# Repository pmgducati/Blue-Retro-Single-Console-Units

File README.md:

# Blue-Retro-Single-Console-Units

This is a collection of PCBs that I made to work with darthcloud's BlueRetro Project. (https://github.com/darthcloud/BlueRetro) The PCB's were created in Eagle and I have included the Gerbers if you would like to create them yourself.

Currently I have NES, Nintendo 64, Gamecube, Sega Saturn, 3DO, PSX/PS2 and PCEngine/Turbografx 16 complete.

I have created PCB's for other supported systems (Listed Below) but have not tested them as I do not have the sytems. I have created a issue for each of the systems that I do not have to test. If you make one please comment in the related issue on any progress/problems.

I am working through Virtual Boy but need to find a cost efficient way to connect it to the Virtual Boy as I am not consolizing mine.

Here is the current status of all systems:

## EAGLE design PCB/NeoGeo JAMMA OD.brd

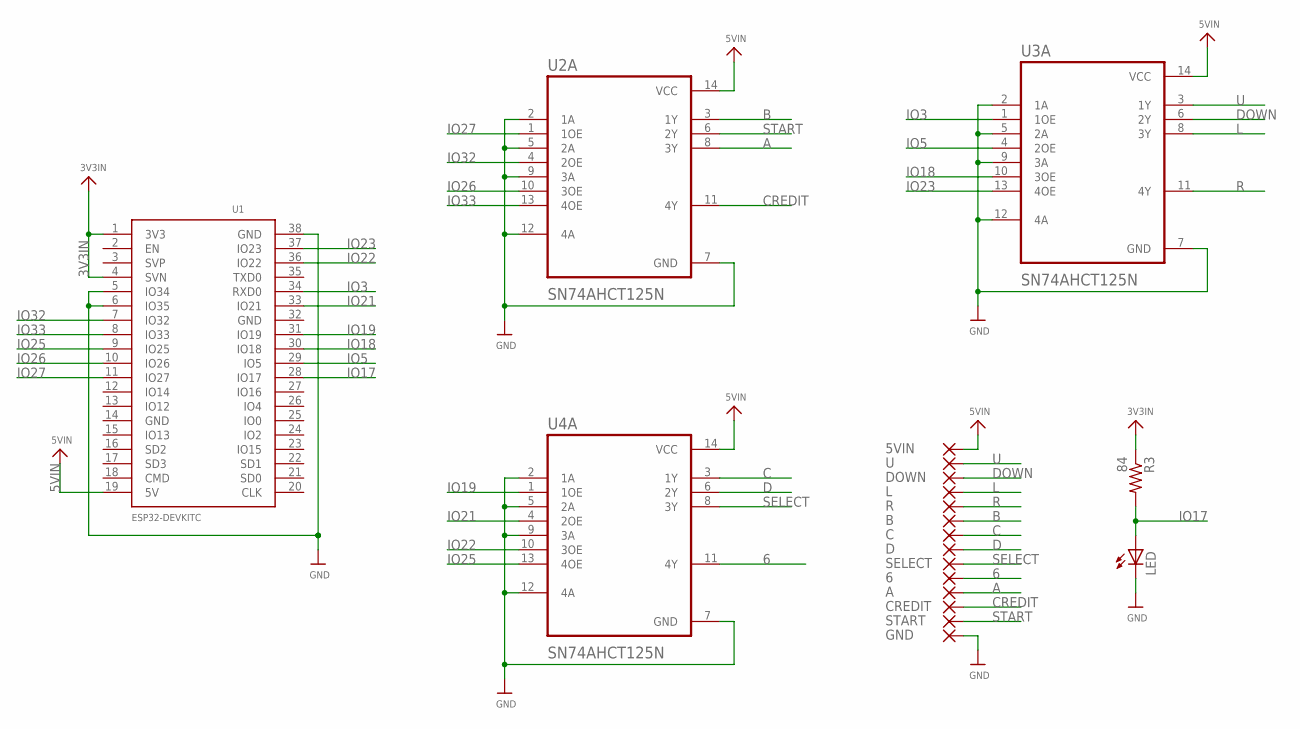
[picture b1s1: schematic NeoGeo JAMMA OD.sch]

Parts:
5VIN, 6: SMD5; SMD2,54-5,08
A: SMD5; SMD2,54-5,08
B: SMD5; SMD2,54-5,08
C: SMD5; SMD2,54-5,08
CREDIT: SMD5; SMD2,54-5,08
D: SMD5; SMD2,54-5,08
DOWN: SMD5; SMD2,54-5,08
GND: SMD5; SMD2,54-5,08
L: SMD5; SMD2,54-5,08
LED: LEDCHIPLED_1206; CHIPLED_1206
R: SMD5; SMD2,54-5,08
R3: 84; R1206
SELECT: SMD5; SMD2,54-5,08
START: SMD5; SMD2,54-5,08
U: SMD5; SMD2,54-5,08
U1: ESP32DEVKITC; ESP32-DEVKITC
U2A, U3A, U4A: SN74AHCT125N; DIP794W45P254L1969H508Q14

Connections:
3V3IN: R3.1, U1.1 (3V3), U1.4 (SVN)
5VIN: 5VIN.1, U1.19 (5V), U2A.14 (VCC), U3A.14 (VCC), U4A.14 (VCC)
6: 6.1, U4A.11 (4Y)
A: A.1, U2A.8 (3Y)
B: B.1, U2A.3 (1Y)
C: C.1, U4A.3 (1Y)
CREDIT: CREDIT.1, U2A.11 (4Y)
D: D.1, U4A.6 (2Y)
DOWN: DOWN.1, U3A.6 (2Y)
GND: GND.1, LED.C, U1.5 (IO34), U1.6 (IO35), U1.38 (GND), U2A.2 (1A), U2A.5 (2A), U2A.7 (GND), U2A.9 (3A), U2A.12 (4A), U3A.2 (1A), U3A.5 (2A), U3A.7 (GND), U3A.9 (3A), U3A.12 (4A), U4A.2 (1A), U4A.5 (2A), U4A.7 (GND), U4A.9 (3A), U4A.12 (4A)
IO3: U1.34 (RXD0), U3A.1 (1OE)
IO5: U1.29 (IO5), U3A.4 (2OE)
IO17: LED.A, R3.2, U1.28 (IO17)
IO18: U1.30 (IO18), U3A.10 (3OE)
IO19: U1.31 (IO19), U4A.1 (1OE)
IO21: U1.33 (IO21), U4A.4 (2OE)
IO22: U1.36 (IO22), U4A.10 (3OE)
IO23: U1.37 (IO23), U3A.13 (4OE)
IO25: U1.9 (IO25), U4A.13 (4OE)
IO26: U1.10 (IO26), U2A.10 (3OE)
IO27: U1.11 (IO27), U2A.1 (1OE)
IO32: U1.7 (IO32), U2A.4 (2OE)
IO33: U1.8 (IO33), U2A.13 (4OE)
L: L.1, U3A.8 (3Y)
R: R.1, U3A.11 (4Y)
SELECT: SELECT.1, U4A.8 (3Y)
START: START.1, U2A.6 (2Y)
U: U.1, U3A.3 (1Y)

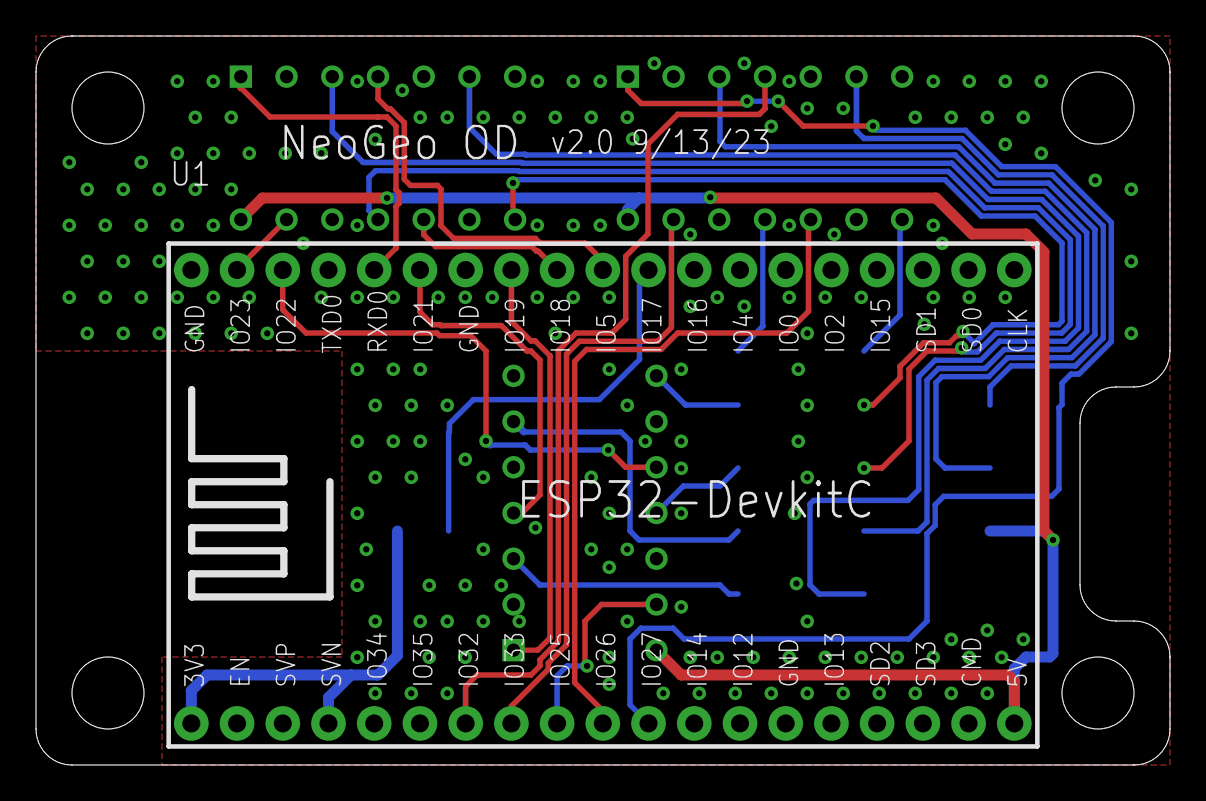
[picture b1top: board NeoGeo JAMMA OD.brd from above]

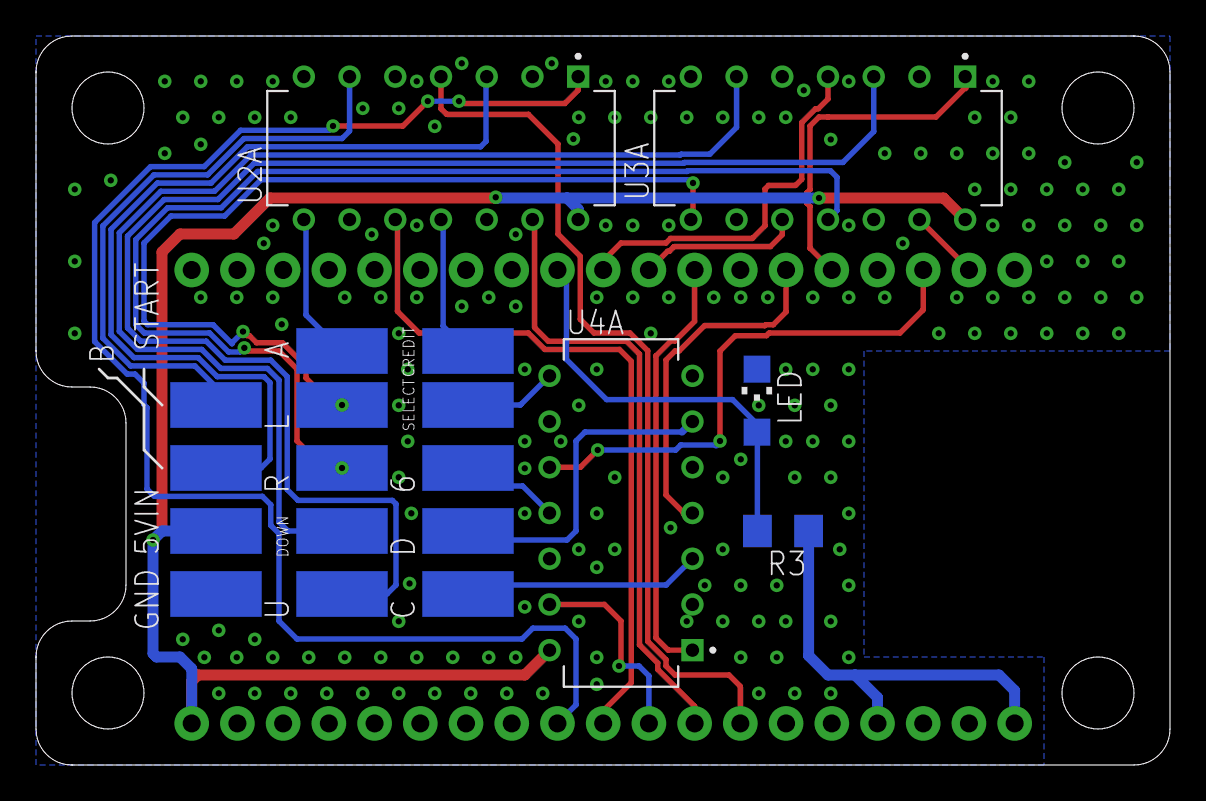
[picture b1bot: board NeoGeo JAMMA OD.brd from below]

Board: 2 copper layers, 63.0 x 40.5 mm, 20 parts (19 on the bottom side), 28 nets.

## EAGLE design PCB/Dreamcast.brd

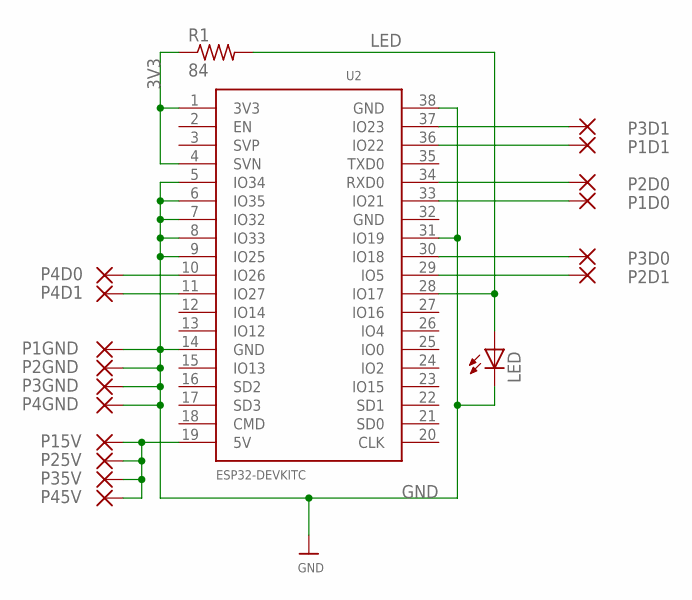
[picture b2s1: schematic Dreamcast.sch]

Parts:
LED: LEDCHIPLED_1206; CHIPLED_1206
P1D0, P1D1, P1GND, P2D0, P2D1, P2GND, P3D0, P3D1, P3GND, P4D0, P4D1, P4GND, P15V, P25V, P35V, P45V: SMD5; SMD2,54-5,08
R1: 84; R1206
U2: ESP32DEVKITC; ESP32-DEVKITC

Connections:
3V3: R1.1, U2.1 (3V3), U2.4 (SVN)
5V: P15V.1, P25V.1, P35V.1, P45V.1, U2.19 (5V)
GND: LED.C, P1GND.1, P2GND.1, P3GND.1, P4GND.1, U2.5 (IO34), U2.6 (IO35), U2.7 (IO32), U2.8 (IO33), U2.9 (IO25), U2.14 (GND), U2.31 (IO19), U2.38 (GND)
LED: LED.A, R1.2, U2.28 (IO17)
P1D0: P1D0.1, U2.33 (IO21)
P1D1: P1D1.1, U2.36 (IO22)
P2D0: P2D0.1, U2.34 (RXD0)
P2D1: P2D1.1, U2.29 (IO5)
P3D0: P3D0.1, U2.30 (IO18)
P3D1: P3D1.1, U2.37 (IO23)
P4D0: P4D0.1, U2.10 (IO26)
P4D1: P4D1.1, U2.11 (IO27)

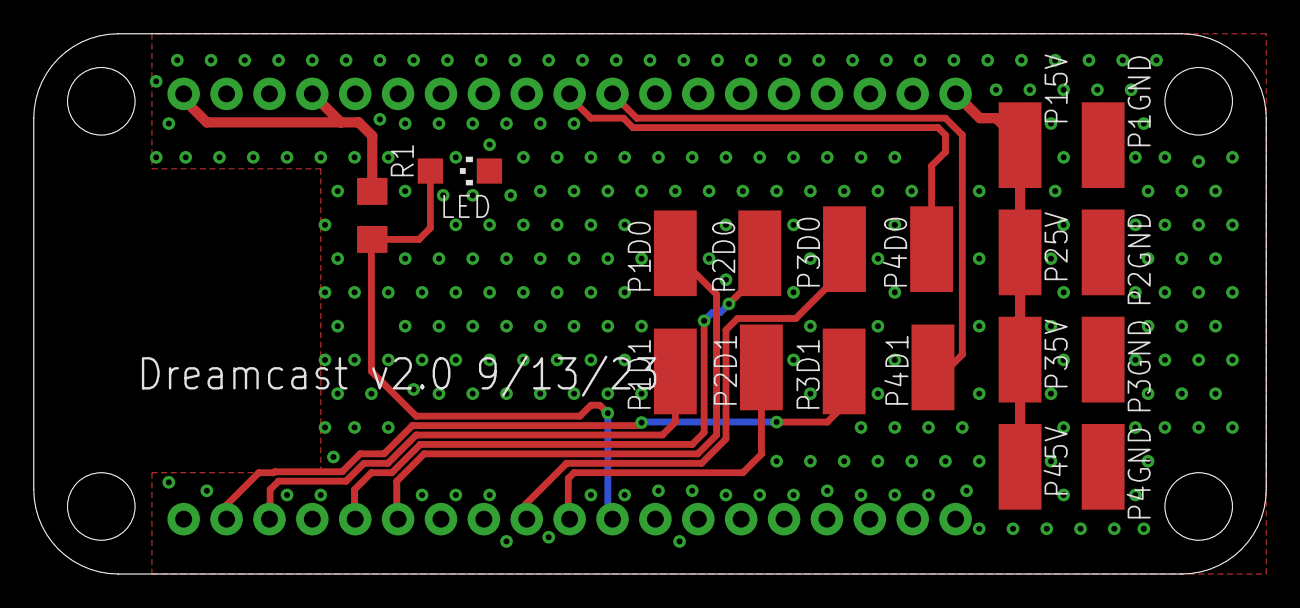
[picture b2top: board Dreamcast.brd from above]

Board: 2 copper layers, 73.0 x 32.0 mm, 19 parts (1 on the bottom side), 12 nets.

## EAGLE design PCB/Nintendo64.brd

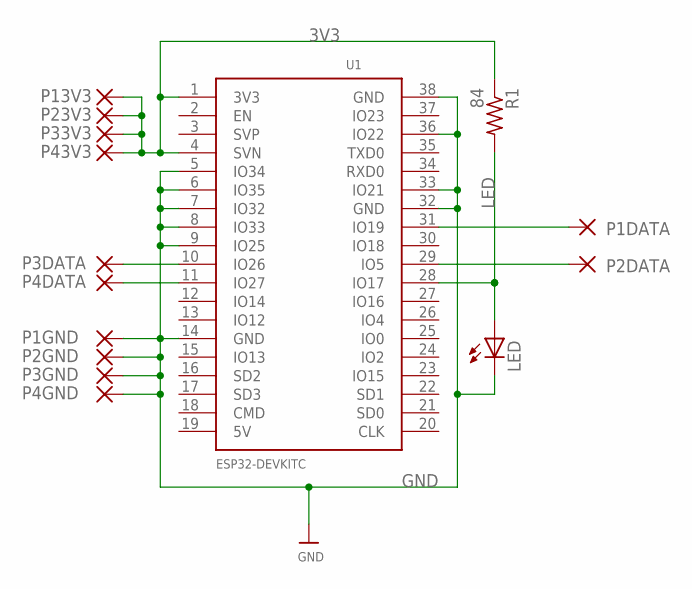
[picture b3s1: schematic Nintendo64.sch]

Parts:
LED: LEDCHIPLED_1206; CHIPLED_1206
P1DATA, P1GND, P2DATA, P2GND, P3DATA, P3GND, P4DATA, P4GND, P13V3, P23V3, P33V3, P43V3: SMD5; SMD2,54-5,08
R1: 84; R1206
U1: ESP32DEVKITC; ESP32-DEVKITC

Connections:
3V3: P13V3.1, P23V3.1, P33V3.1, P43V3.1, R1.1, U1.1 (3V3), U1.4 (SVN); also elsewhere on the board
GND: LED.C, P1GND.1, P2GND.1, P3GND.1, P4GND.1, U1.5 (IO34), U1.6 (IO35), U1.7 (IO32), U1.8 (IO33), U1.9 (IO25), U1.14 (GND), U1.32 (GND), U1.33 (IO21), U1.36 (IO22), U1.38 (GND); also elsewhere on the board
LED: LED.A, R1.2, U1.28 (IO17); also elsewhere on the board
P1DATA: P1DATA.1, U1.31 (IO19); also elsewhere on the board
P2DATA: P2DATA.1, U1.29 (IO5); also elsewhere on the board
P3DATA: P3DATA.1, U1.10 (IO26); also elsewhere on the board
P4DATA: P4DATA.1, U1.11 (IO27); also elsewhere on the board

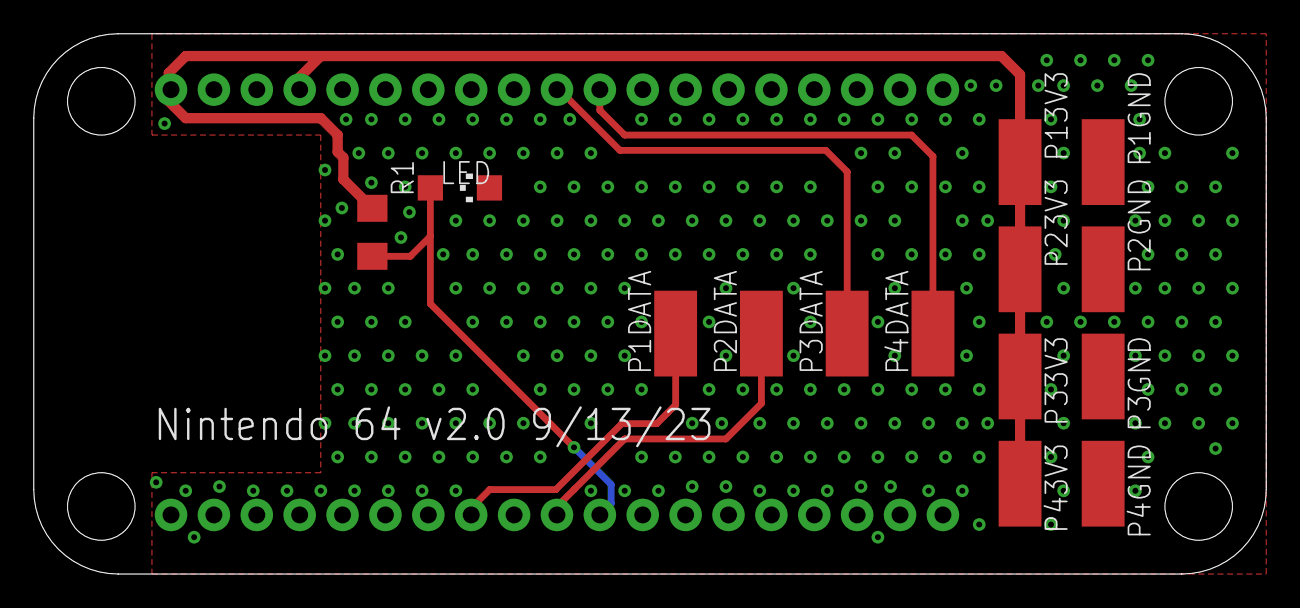
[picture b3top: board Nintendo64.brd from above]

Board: 2 copper layers, 73.0 x 32.0 mm, 15 parts (1 on the bottom side), 7 nets.

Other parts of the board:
U2: ESP32DEVKITC; ESP32-DEVKITC

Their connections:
3V3: U2.1, U2.4; also elsewhere on the board
GND: U2.5, U2.6, U2.7, U2.8, U2.9, U2.14, U2.32, U2.33, U2.36, U2.38; also elsewhere on the board
LED: U2.28; also elsewhere on the board
P1DATA: U2.31; also elsewhere on the board
P2DATA: U2.29; also elsewhere on the board
P3DATA: U2.10; also elsewhere on the board
P4DATA: U2.11; also elsewhere on the board

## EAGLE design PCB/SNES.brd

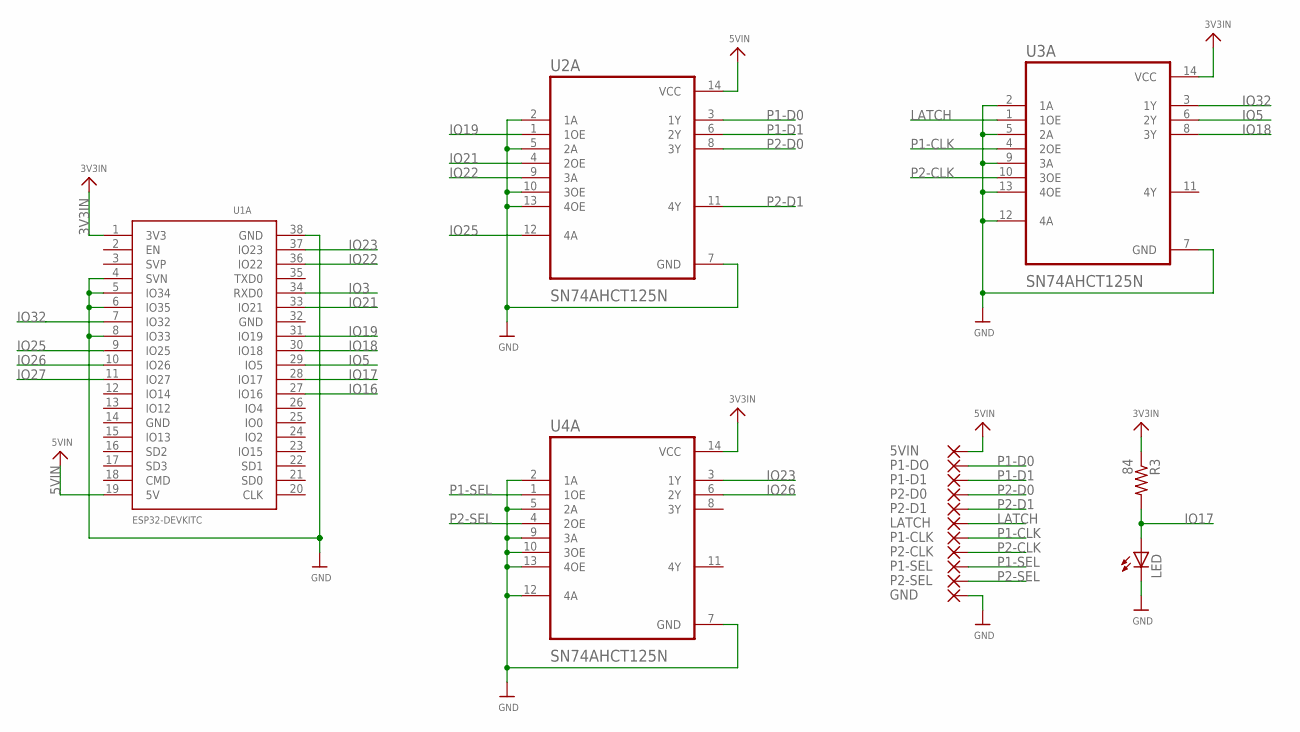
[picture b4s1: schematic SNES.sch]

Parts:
5VIN: SMD5; SMD2,54-5,08
GND: SMD5; SMD2,54-5,08
LATCH: SMD5; SMD2,54-5,08
LED: LEDCHIPLED_1206; CHIPLED_1206
P1-CLK, P1-D1, P1-DO, P1-SEL, P2-CLK, P2-D0, P2-D1, P2-SEL: SMD5; SMD2,54-5,08
R3: 84; R1206
U1A: ESP32DEVKITC; ESP32-DEVKITC
U2A, U3A, U4A: SN74AHCT125N; DIP794W45P254L1969H508Q14

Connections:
3V3IN: R3.1, U1A.1 (3V3), U3A.14 (VCC), U4A.14 (VCC)
5VIN: 5VIN.1, U1A.19 (5V), U2A.14 (VCC)
GND: GND.1, LED.C, U1A.4 (SVN), U1A.5 (IO34), U1A.6 (IO35), U1A.8 (IO33), U1A.38 (GND), U2A.2 (1A), U2A.5 (2A), U2A.7 (GND), U2A.10 (3OE), U2A.13 (4OE), U3A.2 (1A), U3A.5 (2A), U3A.7 (GND), U3A.9 (3A), U3A.12 (4A), U3A.13 (4OE), U4A.2 (1A), U4A.5 (2A), U4A.7 (GND), U4A.9 (3A), U4A.10 (3OE), U4A.12 (4A), U4A.13 (4OE)
IO3: U1A.34 (RXD0)
IO5: U1A.29 (IO5), U3A.6 (2Y)
IO16: U1A.27 (IO16)
IO17: LED.A, R3.2, U1A.28 (IO17)
IO18: U1A.30 (IO18), U3A.8 (3Y)
IO19: U1A.31 (IO19), U2A.1 (1OE)
IO21: U1A.33 (IO21), U2A.4 (2OE)
IO22: U1A.36 (IO22), U2A.9 (3A)
IO23: U1A.37 (IO23), U4A.3 (1Y)
IO25: U1A.9 (IO25), U2A.12 (4A)
IO26: U1A.10 (IO26), U4A.6 (2Y)
IO27: U1A.11 (IO27)
IO32: U1A.7 (IO32), U3A.3 (1Y)
LATCH: LATCH.1, U3A.1 (1OE)
P1-CLK: P1-CLK.1, U3A.4 (2OE)
P1-D0: P1-DO.1, U2A.3 (1Y)
P1-D1: P1-D1.1, U2A.6 (2Y)
P1-SEL: P1-SEL.1, U4A.1 (1OE)
P2-CLK: P2-CLK.1, U3A.10 (3OE)
P2-D0: P2-D0.1, U2A.8 (3Y)
P2-D1: P2-D1.1, U2A.11 (4Y)
P2-SEL: P2-SEL.1, U4A.4 (2OE)

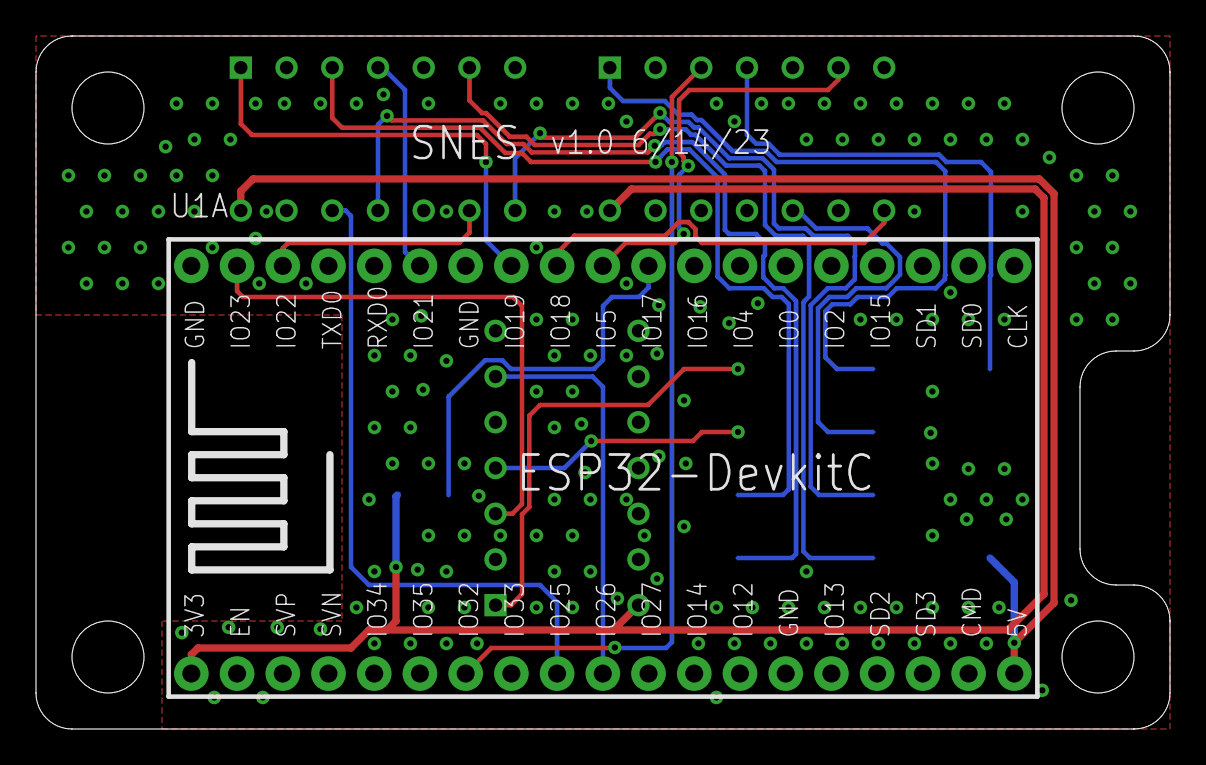
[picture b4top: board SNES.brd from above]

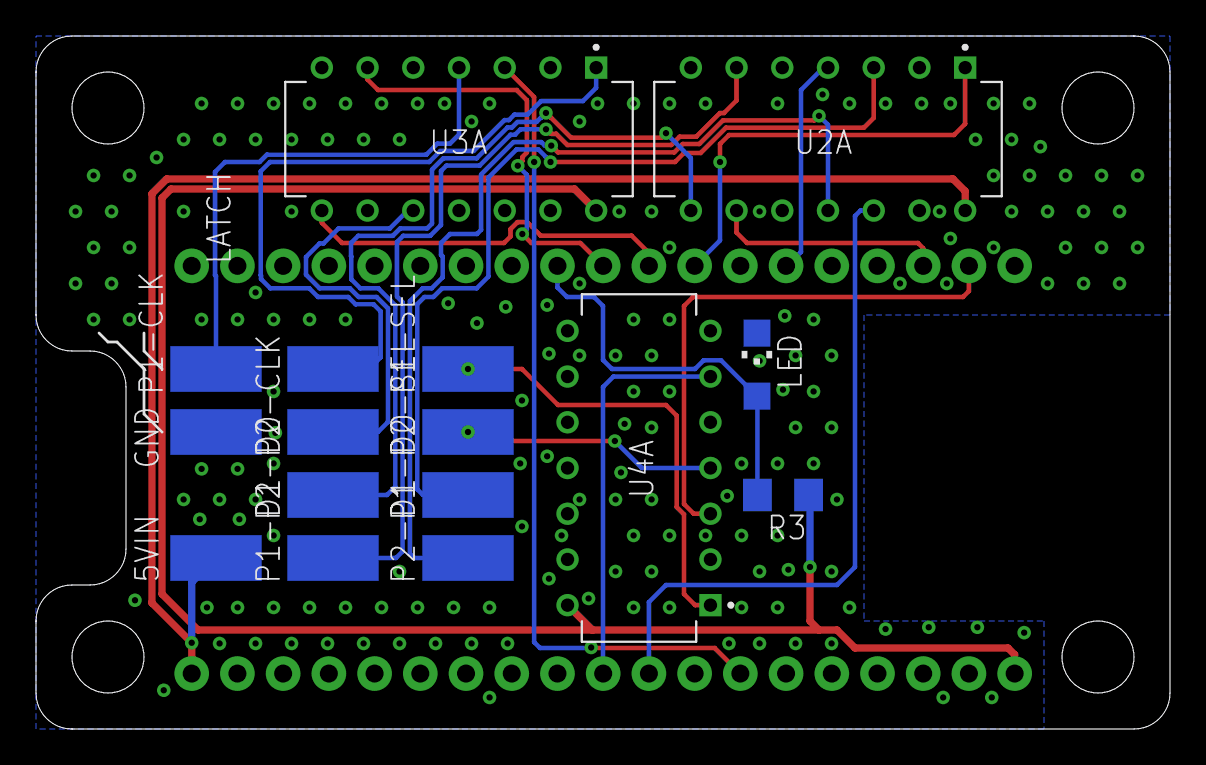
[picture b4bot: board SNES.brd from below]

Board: 2 copper layers, 63.0 x 38.5 mm, 17 parts (16 on the bottom side), 22 nets.

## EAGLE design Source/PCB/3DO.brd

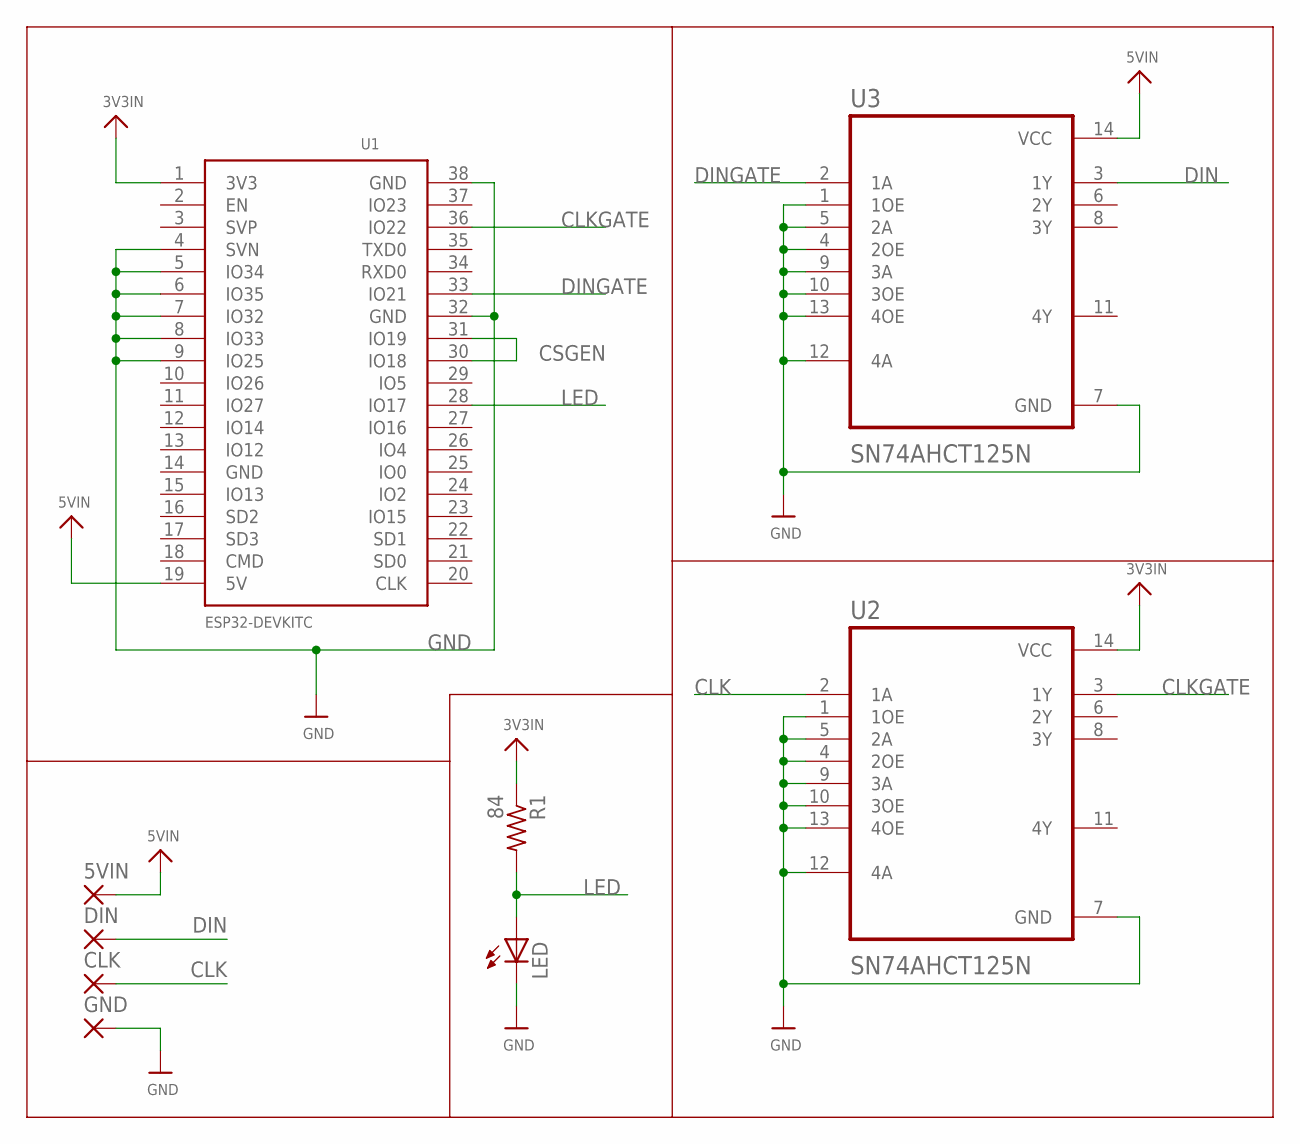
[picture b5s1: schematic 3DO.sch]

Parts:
5VIN: SMD5; SMD2,54-5,08
CLK: SMD5; SMD2,54-5,08
DIN: SMD5; SMD2,54-5,08
GND: SMD5; SMD2,54-5,08
LED: LEDCHIPLED_1206; CHIPLED_1206
R1: 84; R1206
U1: ESP32DEVKITC; ESP32-DEVKITC
U2, U3: SN74AHCT125N; DIP794W45P254L1969H508Q14

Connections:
3V3IN: R1.1, U1.1 (3V3), U2.14 (VCC)
5VIN: 5VIN.1, U1.19 (5V), U3.14 (VCC)
CLK: CLK.1, U2.2 (1A)
CLKGATE: U1.36 (IO22), U2.3 (1Y)
CSGEN: U1.30 (IO18), U1.31 (IO19)
DIN: DIN.1, U3.3 (1Y)
DINGATE: U1.33 (IO21), U3.2 (1A)
GND: GND.1, LED.C, U1.4 (SVN), U1.5 (IO34), U1.6 (IO35), U1.7 (IO32), U1.8 (IO33), U1.9 (IO25), U1.32 (GND), U1.38 (GND), U2.1 (1OE), U2.4 (2OE), U2.5 (2A), U2.7 (GND), U2.9 (3A), U2.10 (3OE), U2.12 (4A), U2.13 (4OE), U3.1 (1OE), U3.4 (2OE), U3.5 (2A), U3.7 (GND), U3.9 (3A), U3.10 (3OE), U3.12 (4A), U3.13 (4OE)
LED: LED.A, R1.2, U1.28 (IO17)

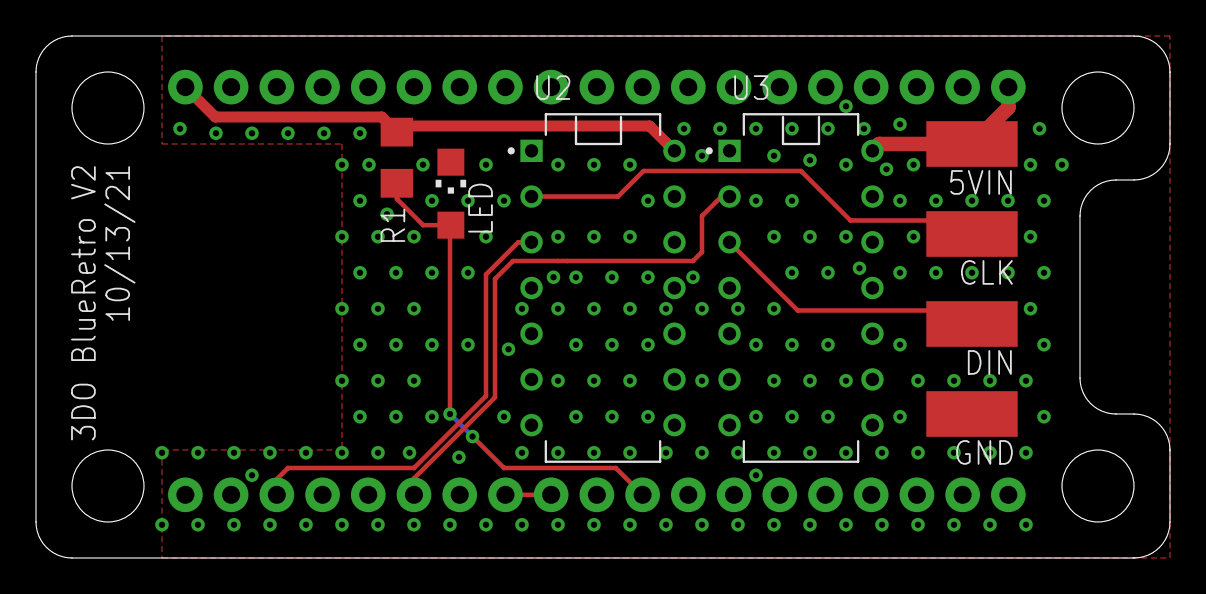
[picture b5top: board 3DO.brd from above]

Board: 2 copper layers, 63.0 x 29.0 mm, 9 parts (1 on the bottom side), 9 nets.

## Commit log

2021-10-13 Initial Upload
2022-05-03 New PCBs & House Keeping
    Created New PCBs for Atari 2600 (PP/OD), CD-i, Dreamcast, NES, N64, PC-FX and PSX/PS2.
    Rearranged files to better match AIO Repo
2022-05-03 Raw Links -> Link References
2022-05-03 Replaced Image Of Statuses With Status Table
2022-05-03 Moved Status In Dedicated File & Added Quicklinks
2022-05-03 Formatted Completed Section
2022-05-03 Tidied Up FileSystem
2022-05-03 General Formatting
2022-05-03 Removed Redundant Status File
2022-08-03 Formatted README
2022-08-03 Adjusted Layout
2022-08-03 Adjusted Spacing
2023-06-15 New PCB Versions
    Adding SG-1000/SMS, SNES and Genesis (Per PCESlayer's Request). Eagle Files and Gerbers are included. BOM has been removed and can be referenced in the AIO repository.
2023-06-16 Genesis Gerber
    Adding the Genesis Gerber file. It was missed in the last commit
2023-08-29 Neo Geo OD Standalone
    Create per tr12345's request in the AIO thread
2023-08-29 Updated Project Status
2023-09-13 ESP Size Change
    The original design used an ESP with a 22mm spacing, Updated the part to the standard version with 25mm spacing.
2023-09-13 Update version Callout and date on PCB
2023-11-28 Updated PCBs

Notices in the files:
parts and their libraries:
microbuilder: This work is placed in the public domain, and may be freely used for commercial and non-commercial work with the following conditions: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
